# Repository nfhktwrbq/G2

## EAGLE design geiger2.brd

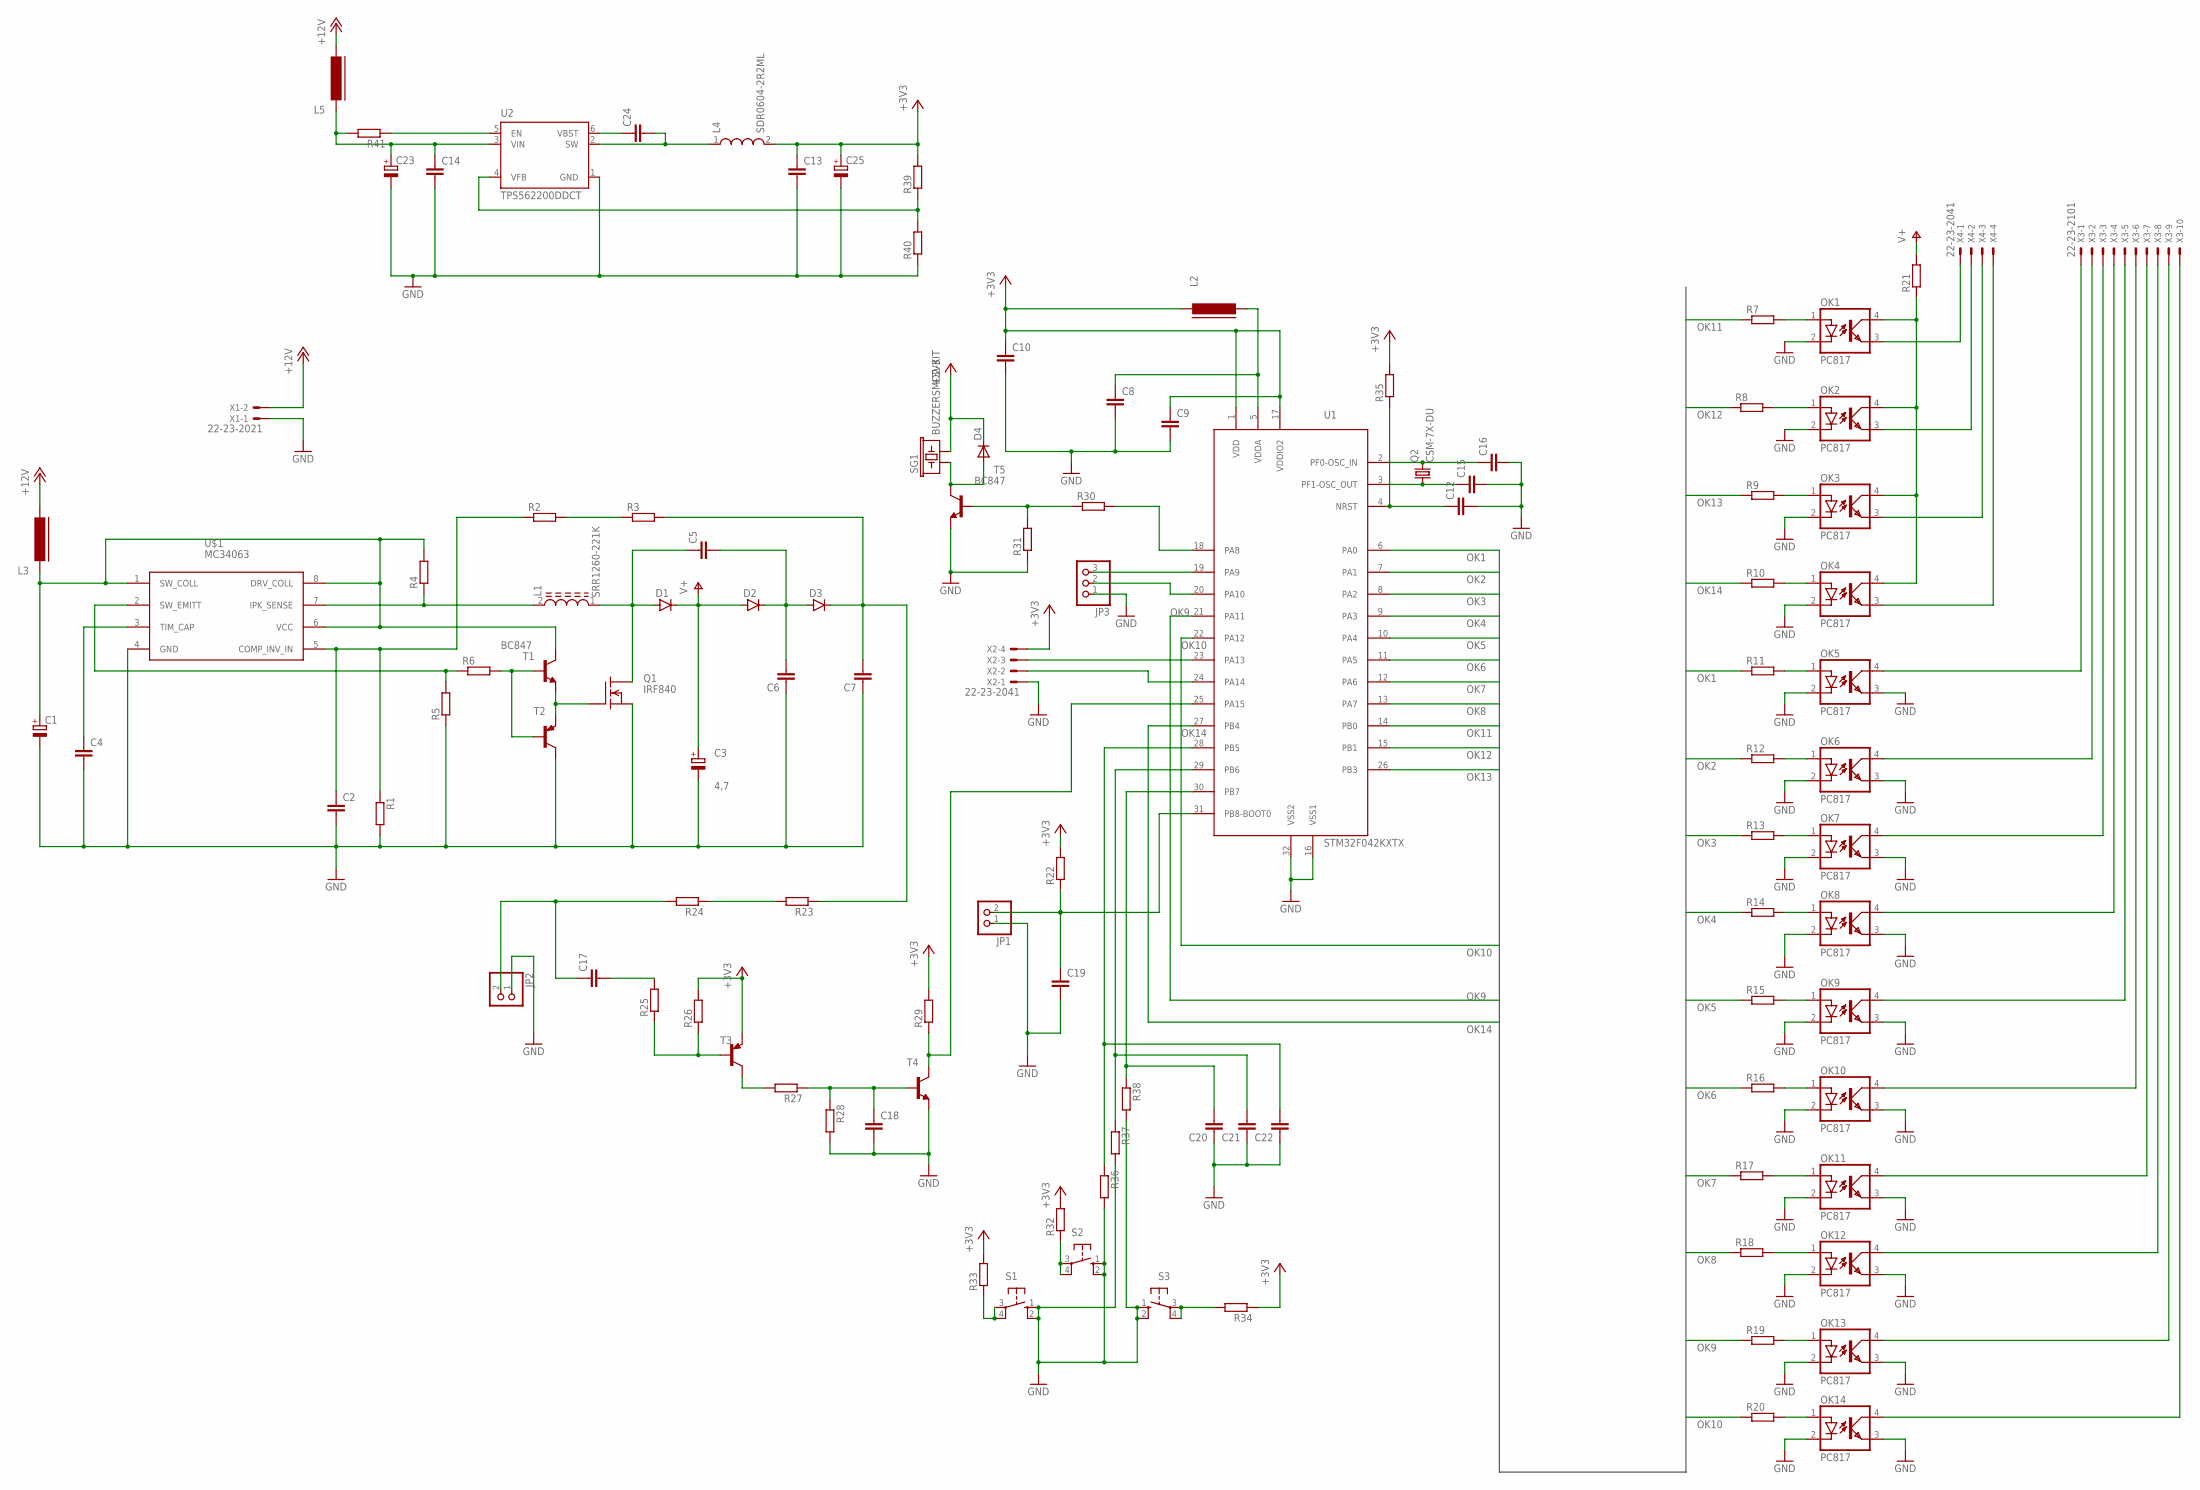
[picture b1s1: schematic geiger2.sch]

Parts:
C1, C23, C25: CPOL-EUCT7343; CT7343
C2, C4, C8, C9, C10, C12, C13, C14, C15, C16, C24: C-EUC0805; C0805
C3: 4,7; E5-10,5
C5, C6, C7: C-EUC1812K; C1812K
C17: C-EUC1206K; C1206K
C18, C19, C20, C21, C22: C-EUC0805K; C0805K
D1, D2, D3: DIODE-DO214AC; DO214AC
D4: DIODE-SOD-123; SOD-123
JP1, JP2: PINHD-1X2; 1X02
JP3: PINHD-1X3; 1X03
L1: SRR1260-221K; INDP125125X600N
L2, L3, L5: FERRITE-0805; FB805
L4: SDR0604-2R2ML; INDP5858X480N
OK1, OK2, OK3, OK4, OK5, OK6, OK7, OK8, OK9, OK10, OK11, OK12, OK13, OK14: PC817; DIL04
Q1: IRF840; TO220
Q2: CSM-7X-DU
R1, R2, R3, R5, R6, R7, R8, R9, R10, R11, R12, R13, R14, R15, R16, R17, R18, R19, R20, R22, R25, R26, R27, R28, R29, R30, R31, R32, R33, R34, R35, R36, R37, R38, R39, R40, R41: R-EU_R0805; R0805
R4: R-EU_R2512; R2512
R21, R23, R24: R-EU_R1206; R1206
S1, S2, S3: 10-XX; B3F-10XX
SG1: BUZZERSMD2-KIT; BUZZER-CCV-KIT
T1, T5: BC847; SOT23
T2: BC857C-PNP-SOT23-BEC; SOT23-BEC
T3: BC857A-PNP-SOT23-BEC; SOT23-BEC
T4: BC847-NPN-SOT23-BEC; SOT23-BEC
U1: STM32F042KXTX; LQFP32
U2: TPS562200DDCT; SOT95P280X110-6N
U$1: MC34063; SO-8
X1: 22-23-2021
X2, X4: 22-23-2041
X3: 22-23-2101

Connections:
+3V3: C9.1, C10.1, C13.1, C25.+, D4.C, L2.1, L4.2, R22.2, R26.2, R29.2, R32.2, R33.2, R34.1, R35.2, R39.2, SG1.- (2), T3.E, U1.1 (VDD), U1.17 (VDDIO2), X2.4
+12V: L3.2, L5.2, X1.2
GND: C1.-, C2.2, C3.-, C4.2, C6.1, C7.1, C8.2, C9.2, C10.2, C12.2, C13.2, C14.2, C15.2, C16.2, C18.2, C19.2, C20.1, C21.1, C22.1, C23.-, C25.-, JP1.1, JP2.1, JP3.1, OK1.2 (C), OK2.2 (C), OK3.2 (C), OK4.2 (C), OK5.2 (C), OK5.3 (EMIT), OK6.2 (C), OK6.3 (EMIT), OK7.2 (C), OK7.3 (EMIT), OK8.2 (C), OK8.3 (EMIT), OK9.2 (C), OK9.3 (EMIT), OK10.2 (C), OK10.3 (EMIT), OK11.2 (C), OK11.3 (EMIT), OK12.2 (C), OK12.3 (EMIT), OK13.2 (C), OK13.3 (EMIT), OK14.2 (C), OK14.3 (EMIT), Q1.3 (S), R1.2, R5.1, R28.2, R31.1, R36.2, R37.2, R38.2, R40.1, S1.1 (S), S1.2 (S1), S2.1 (S), S2.2 (S1), S3.1 (S), S3.2 (S1), T2.C, T4.E, T5.2 (E), U1.16 (VSS1), U1.32 (VSS2), U2.1 (GND), U$1.4 (GND), X1.1, X2.1
unnamed: C2.1, R1.1, R2.1, U$1.5 (COMP_INV_IN)
unnamed: C7.2, D3.C, R3.2, R23.1
unnamed: R6.2, T1.1 (B), T2.B
unnamed: R5.2, R6.1, U$1.2 (SW_EMITT)
unnamed: L1.2, R4.1, U$1.7 (IPK_SENSE)
unnamed: Q1.1 (G), T1.2 (E), T2.E
unnamed: C5.1, D1.A, L1.1, Q1.2 (D)
unnamed: OK1.3 (EMIT), X4.1
unnamed: C14.1, C23.+, L5.1, R41.2, U2.3 (VIN)
unnamed: R2.2, R3.1
unnamed: C4.1, U$1.3 (TIM_CAP)
unnamed: C5.2, C6.2, D2.C, D3.A
unnamed: C12.1, R35.1, U1.4 (NRST)
unnamed: OK14.1 (A), R20.2
unnamed: OK13.1 (A), R19.2
unnamed: OK12.1 (A), R18.2
unnamed: OK11.1 (A), R17.2
unnamed: C1.+, L3.1, R4.2, T1.3 (C), U$1.1 (SW_COLL), U$1.6 (VCC), U$1.8 (DRV_COLL)
unnamed: OK10.1 (A), R16.2
unnamed: OK9.1 (A), R15.2
unnamed: OK8.1 (A), R14.2
unnamed: OK7.1 (A), R13.2
unnamed: OK6.1 (A), R12.2
unnamed: OK5.1 (A), R11.2
unnamed: OK4.1 (A), R10.2
unnamed: OK3.1 (A), R9.2
unnamed: OK2.1 (A), R8.2
unnamed: OK1.1 (A), R7.2
unnamed: OK1.4 (COL), OK2.4 (COL), OK3.4 (COL), OK4.4 (COL), R21.1
unnamed: U1.23 (PA13), X2.3
unnamed: U1.24 (PA14), X2.2
unnamed: OK2.3 (EMIT), X4.2
unnamed: OK3.3 (EMIT), X4.3
unnamed: OK4.3 (EMIT), X4.4
unnamed: C15.1, Q2.1, U1.3 (PF1-OSC_OUT)
unnamed: OK5.4 (COL), X3.1
unnamed: OK6.4 (COL), X3.2
unnamed: OK7.4 (COL), X3.3
unnamed: OK8.4 (COL), X3.4
unnamed: OK9.4 (COL), X3.5
unnamed: OK10.4 (COL), X3.6
unnamed: OK11.4 (COL), X3.7
unnamed: OK12.4 (COL), X3.8
unnamed: OK13.4 (COL), X3.9
unnamed: OK14.4 (COL), X3.10
unnamed: C16.1, Q2.2, U1.2 (PF0-OSC_IN)
unnamed: C19.1, JP1.2, R22.1, U1.31 (PB8-BOOT0)
unnamed: R23.2, R24.1
unnamed: C17.1, JP2.2, R24.2
unnamed: R27.2, T3.C
unnamed: C17.2, R25.2
unnamed: R25.1, R26.1, T3.B
unnamed: C18.1, R27.1, R28.1, T4.B
unnamed: JP3.3, U1.19 (PA9)
unnamed: JP3.2, U1.20 (PA10)
unnamed: R29.1, T4.C, U1.25 (PA15)
unnamed: R30.2, U1.18 (PA8)
unnamed: R30.1, R31.2, T5.1 (B)
unnamed: R33.1, S1.3, S1.4 (P1)
unnamed: C22.2, R36.1, U1.28 (PB5)
unnamed: D4.A, SG1.+ (1), T5.3 (C)
unnamed: R32.1, S2.3, S2.4 (P1)
unnamed: R34.2, S3.3, S3.4 (P1)
unnamed: C21.2, R37.1, U1.29 (PB6)
unnamed: C20.2, R38.1, U1.30 (PB7)
unnamed: C8.1, L2.2, U1.5 (VDDA)
unnamed: R41.1, U2.5 (EN)
unnamed: C24.1, U2.6 (VBST)
unnamed: C24.2, L4.1, U2.2 (SW)
unnamed: R39.1, R40.2, U2.4 (VFB)
OK1: R11.1, U1.6 (PA0)
OK2: R12.1, U1.7 (PA1)
OK3: R13.1, U1.8 (PA2)
OK4: R14.1, U1.9 (PA3)
OK5: R15.1, U1.10 (PA4)
OK6: R16.1, U1.11 (PA5)
OK7: R17.1, U1.12 (PA6)
OK8: R18.1, U1.13 (PA7)
OK9: R19.1, U1.21 (PA11)
OK10: R20.1, U1.22 (PA12)
OK11: R7.1, U1.14 (PB0)
OK12: R8.1, U1.15 (PB1)
OK13: R9.1, U1.26 (PB3)
OK14: R10.1, U1.27 (PB4)
V+: C3.+, D1.C, D2.A, R21.2

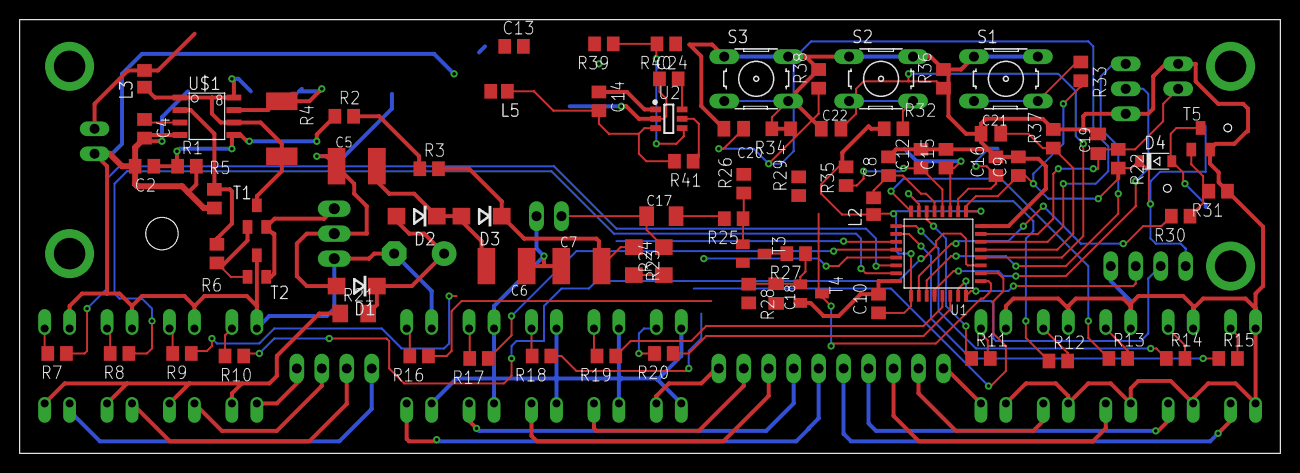
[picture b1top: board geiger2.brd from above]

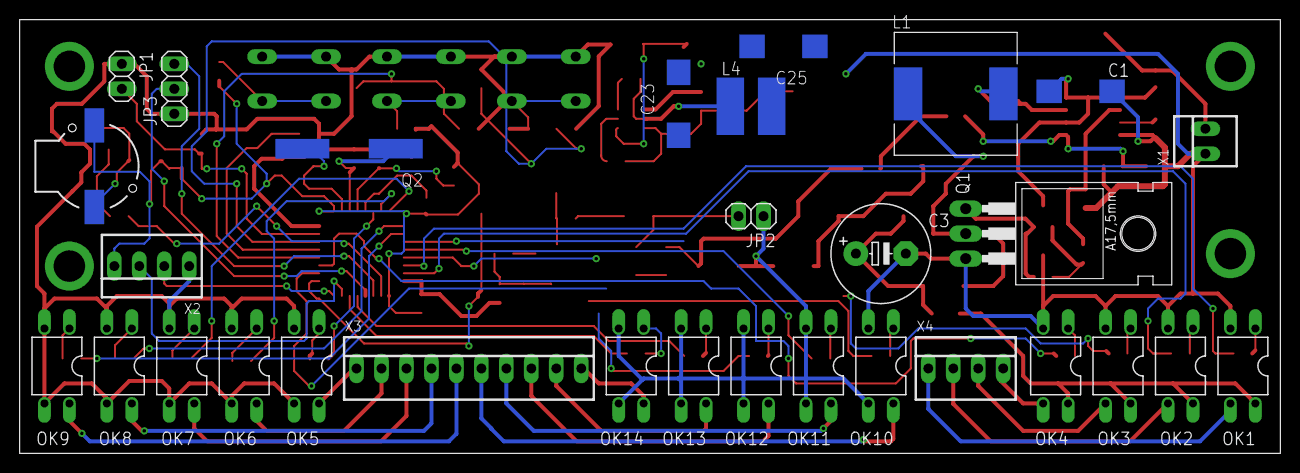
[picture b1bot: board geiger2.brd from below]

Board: 2 copper layers, 128.2 x 44.1 mm, 109 parts (30 on the bottom side), 88 nets.

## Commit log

2019-05-13 Add scheme eagle files
2019-05-17 Finish schematic v1.0
2019-05-17 Edit schematic
2019-05-31 Edit mosfet driver
2019-06-01 Edit DC-DC
2019-06-01 Edit inductor
2019-06-02 Add pcb and place elements
2019-06-07 Edit board
2019-06-08 Add routing

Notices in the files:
parts and their libraries:
SparkFun: Licensing: CC v3.0 Share-Alike You are welcome to use this library for commercial purposes.
